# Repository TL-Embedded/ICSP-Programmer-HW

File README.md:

# ICSP-Programmer-HW

This is a ICSP programming board for AVR targets.

The processor onboard is an ATMEGA8A, and can be programmed using another ICSP-Programmer.

# Connector

The connector is laid out as per a standard Arduino ICSP programmer, so this can to program AVR Arduinos via IDC ribbon cable. This can also be combined with a TC2030 cable for a tag connect solution.

The ICSP connector is laid out as follows:

| Function | Pin # | Pin # | Function |
| -------- | ----- | ----- | -------- |
| MISO     | 1     | 2     | VCC      |
| SCK      | 3     | 4     | MOSI     |
| NRST     | 5     | 6     | GND      |

# Target VCC

The programmer powered via 5V from USB, but does **not** power the target by default. The `VCC` pin is used for voltage reference. The target voltage may be anywhere between 1.8V and 5.5V.

The labeled `VCC` pin can be used to inject voltage to the target. Alternately the jumper `JP1` can be shorted to tie `VCC` to USB 5V.

# USB

The USB C connector operates in USB 2.0 legacy mode. A FTDI `FT230QX` chip provides a serial port interface.

Drivers for the FTDI chip can be found [here](https://ftdichip.com/drivers/).

# Firmware

The firmware for this PCB is [ICSP-FW.hex](./firmware/ICSP-FW.hex).
See the usage section for an example of programming a ICSP programmer from another programmer.

Note: To Program a ICSP programmer, its target `VCC` must *not* be powered. Ensure that `JP1` is open, and no power is provided via the `VCC` pin or ICSP connector.

# Usage

The windows executable version of [avrdude](https://github.com/avrdudes/avrdude) is included in this repo to flash a target.

You will need to substitute your serial port and target information.

An example for flashing the ICSP firmware is below:
```sh
# Verify the target is connected.
.\avrdude.exe -C "avrdude.conf" -c avrisp -P COM3 -b 115200 -p ATMEGA8

# Configure the target fuses.
# This is required to set the oscillator config
.\avrdude.exe -C "avrdude.conf" -c avrisp -P COM3 -b 115200 -p ATMEGA8 -U lfuse:w:0xbe:m -U hfuse:w:0xd9:m

# Flash the target with 'ICSP-FW.hex'
.\avrdude.exe -C "avrdude.conf" -c avrisp -P COM3 -b 115200 -p ATMEGA8 -U flash:w:ICSP-FW.hex:i
```

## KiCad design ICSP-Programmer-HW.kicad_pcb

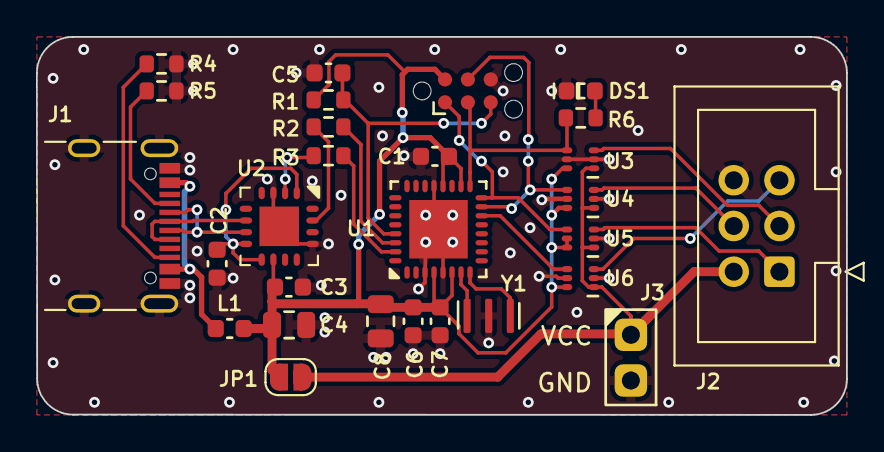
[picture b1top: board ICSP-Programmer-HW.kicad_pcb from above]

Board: 2 copper layers, 45.0 x 21.0 mm, 28 parts (0 on the bottom side), 25 nets.

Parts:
C1, C2, C3, C5, C6, C7: 100n; C_0603
C4, C8: 10u; C_0805
DS1: LED_GRN; DS_0603
J1: USB4105-GF-A-060; USB_C_USB4105-GF-A-060
J2: 61200621621; IDC-Header_2x03_P2.54mm_Vertical
J3: Pins_2.54_1x2; Pins-2.54-1x2
JP1: SolderJumper2; SolderJumper-2_P1.3mm_Open_RoundedPad1.0x1.5mm
L1: 600R; FB_0603
N1: TC2030_NL_SWD; TagConnect_TC2030_NL
R1: 10K; R_0603
R2, R3: 1K; R_0603
R4, R5: 5K1; R_0603
R6: 470R; R_0603
U1: ATMEGA8A-MU; QFN32_05_5x5_EP
U2: FT230XQ; QFN16_065_4x4_EP
U3, U4, U5, U6: 74LVC1T45Z6; SOT563
Y1: CSTNE16M0V530000R0; Oscillator_SMD3_3.2x1.3

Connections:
+3.3V: C2.1, U2.1 (VCCIO), U2.8 (3V3OUT), U2.9 (NRST)
+5V: C1.1, C3.1, C4.1, C6.1, C7.1, C8.1, JP1.1 (A), L1.2, N1.2, R1.1, U1.4 (VCC), U1.6 (VCC), U1.18 (AVCC), U1.20 (AREF), U2.10 (VCC), U3.6 (VCCB), U4.6 (VCCB), U5.5 (DIR), U5.6 (VCCB), U6.6 (VCCB)
/MCU/ICSP_MISO: N1.1, U1.16 (PB4/MISO), U5.4 (B)
/MCU/ICSP_MOSI: N1.4, U1.15 (PB3/MOSI), U4.4 (B)
/MCU/ICSP_NRST: C5.1, N1.5, R1.2, U1.29 (NRST/PC5)
/MCU/ICSP_SCK: N1.3, R6.1, U1.17 (SCK/PB5), U3.4 (B)
/MCU/RX: R2.2, U1.30 (RXD/PD0)
/MCU/TARGET_NRST: U1.14 (PB2), U6.4 (B)
/MCU/TX: R3.1, U1.31 (TXD/PD1)
/Target/TARGET_MISO: J2.1, U5.3 (A)
/Target/TARGET_MOSI: J2.4, U4.3 (A)
/Target/TARGET_NRST: J2.5, U6.3 (A)
/Target/TARGET_SCK: J2.3, U3.3 (A)
/Target/TARGET_VCC: J2.2, J3.1, JP1.2 (B), U3.1 (VCCA), U4.1 (VCCA), U5.1 (VCCA), U6.1 (VCCA)
/USB/USB_DM: J1.A7 (D-), J1.B7 (D-), U2.7 (USBDM)
/USB/USB_DP: J1.A6 (D+), J1.B6 (D+), U2.6 (USBDP)
GND: C1.2, C2.2, C3.2, C4.2, C5.2, C6.2, C7.2, C8.2, DS1.1 (K), J1.A1 (GND), J1.A12 (GND), J1.S (SHIELD), J2.6, J3.2, N1.6, R4.2, R5.2, U1.3 (GND), U1.5 (GND), U1.21 (GND), U1.33 (EP), U2.3 (GND), U2.13 (GND), U2.17 (GND), U3.2 (GND), U3.5 (DIR), U4.2 (GND), U4.5 (DIR), U5.2 (GND), U6.2 (GND), U6.5 (DIR), Y1.2
unnamed: DS1.2 (A), R6.2
unnamed: J1.A5 (CC1), R5.1
unnamed: J1.B5 (CC2), R4.1
unnamed: J1.A4 (VBUS), J1.A9 (VBUS), L1.1
unnamed: U1.7 (PB7/XTAL1), Y1.1
unnamed: U1.8 (PB7/XTAL2), Y1.3
unnamed: R3.2, U2.2 (RXD)
unnamed: R2.1, U2.15 (TXD)

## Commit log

2023-07-04 Do PCB
2023-07-04 Update readme
    Add jumper to tie 5V to VCC
2023-07-04 Update output script
2023-07-08 Include avrdude and instructions
2023-07-18 Fix direction issue on MISO/MOSI
2023-07-18 Add notes on programming
2023-07-18 PCB version to 1.1
